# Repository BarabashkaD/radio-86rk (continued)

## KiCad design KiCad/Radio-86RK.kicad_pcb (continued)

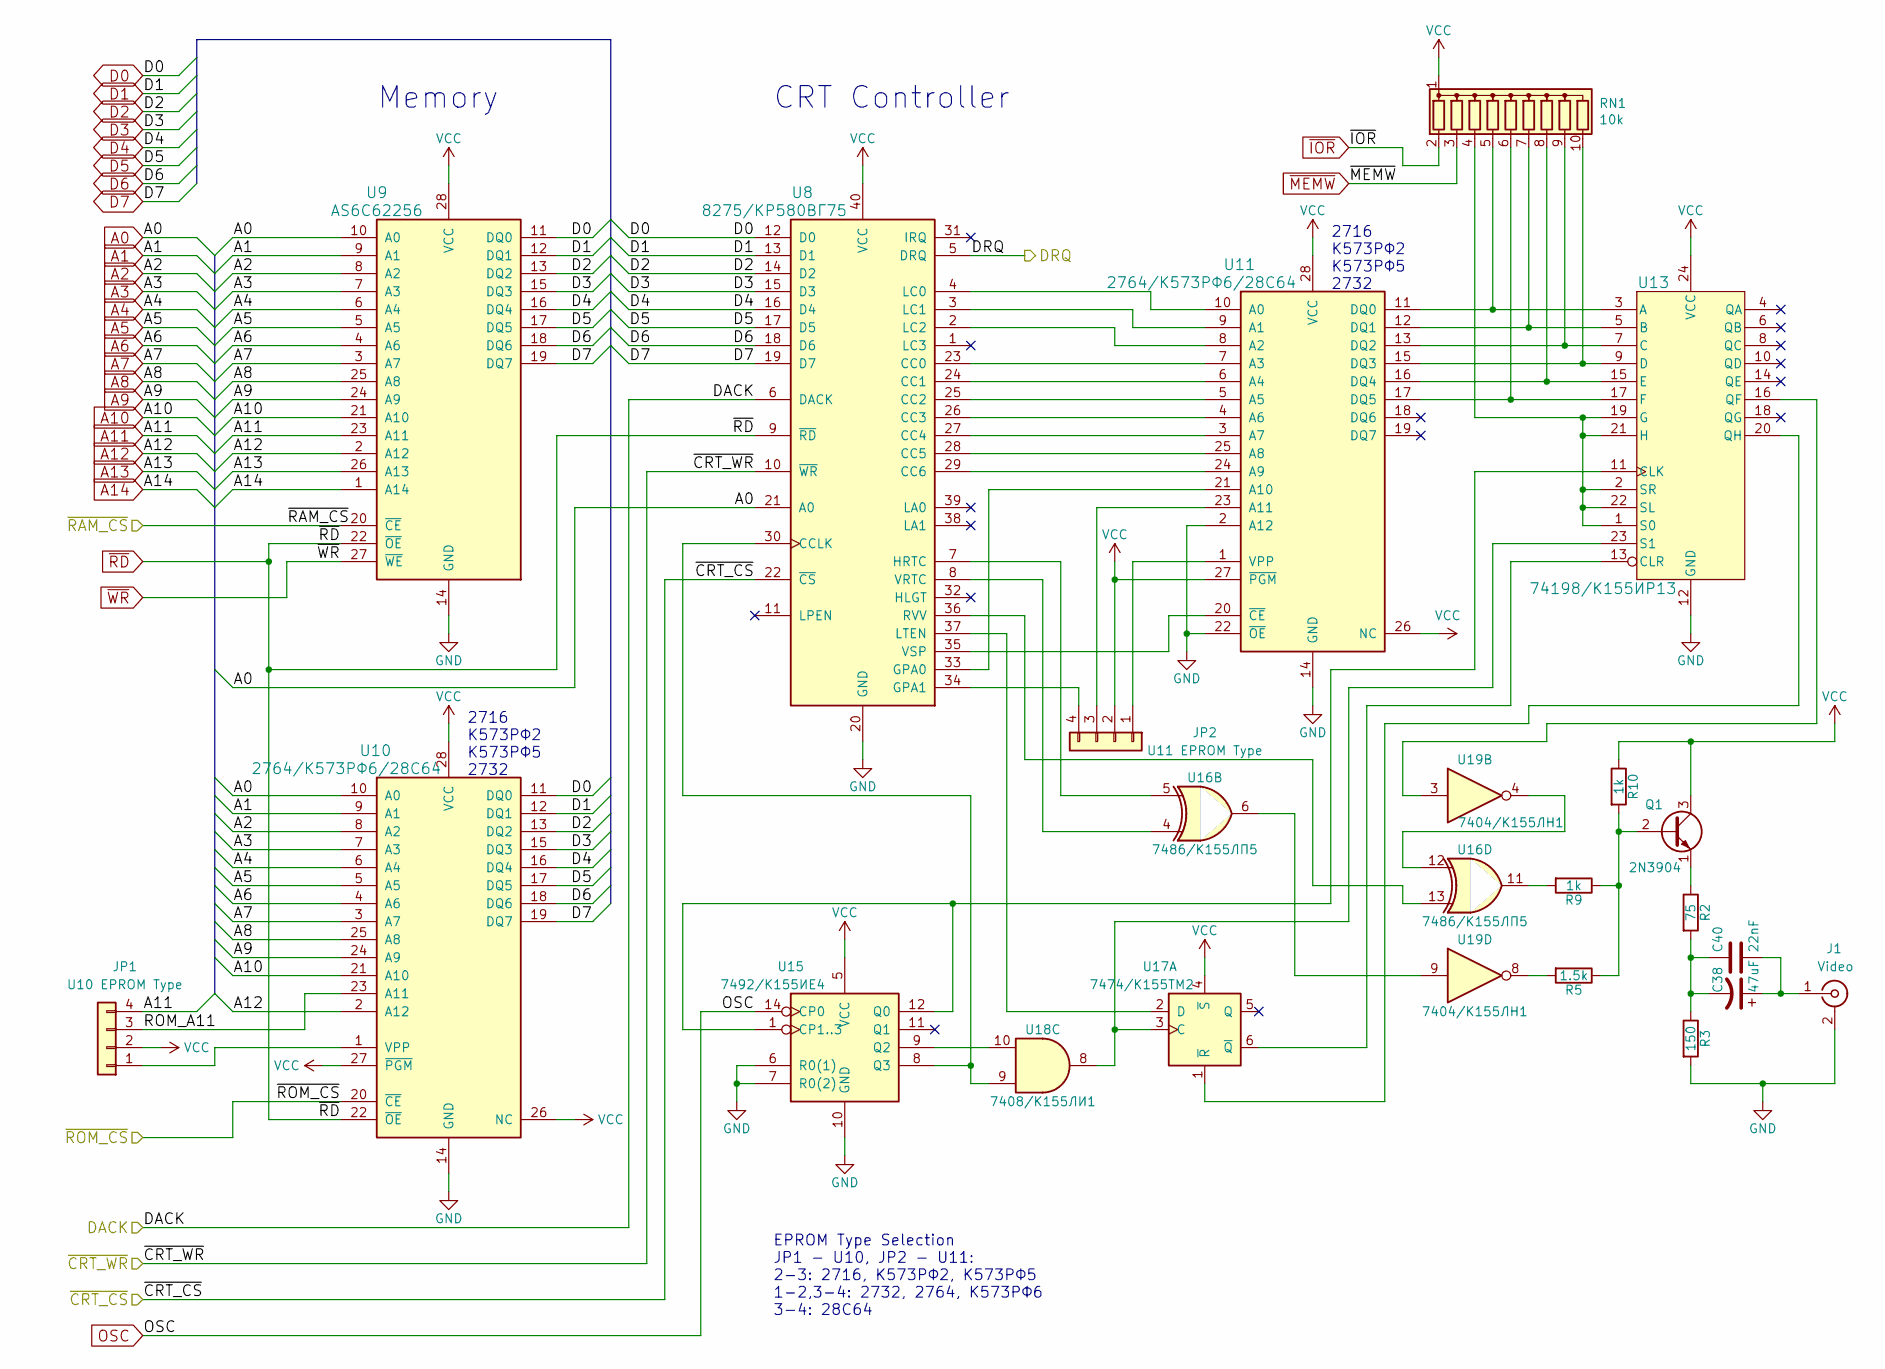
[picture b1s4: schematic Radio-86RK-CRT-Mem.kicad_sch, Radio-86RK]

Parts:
C38: 47uF; Cap_Elec_Radial_6.3mm
C40: 22nF; Cap_Cer_508
J1: Video; Conn_RCA_Right
JP1: U10 EPROM Type; Conn_Pin_Header_4x1_2.54mm
JP2: U11 EPROM Type; Conn_Pin_Header_4x1_2.54mm
Q1: 2N3904; Transistor_TO92_EBC_254
R2: 75; Res_762
R3: 150; Res_762
R5: 1.5k; Res_762
R9, R10: 1k; Res_762
RN1: 10k; Conn_SIL10
U8: 8275/КР580ВГ75; IC_DIP40_600
U9: AS6C62256; IC_DIP28_600
U10, U11: 2764/К573РФ6/28C64; IC_DIP28_600
U13: 74198/К155ИР13; IC_DIP24_600
U15: 7492/К155ИЕ4; IC_DIP14_300
U16: 7486/К155ЛП5; IC_DIP14_300
U17: 7474/К155ТМ2; IC_DIP14_300
U18: 7408/К155ЛИ1; IC_DIP14_300
U19: 7404/К155ЛН1; IC_DIP14_300

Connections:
/CRT_Memory/ROM_A11: JP1.3, U10.23 (A11)
/DACK: U8.6 (DACK); also elsewhere on the board
/DRQ: U8.5 (DRQ); also elsewhere on the board
/~CRT_CS: U8.22 (~CS); also elsewhere on the board
/~CRT_WR: U8.10 (~WR); also elsewhere on the board
/~RAM_CS: U9.20 (~CE); also elsewhere on the board
/~ROM_CS: U10.20 (~CE); also elsewhere on the board
A0: U8.21 (A0), U9.10 (A0), U10.10 (A0); also elsewhere on the board
A1: U9.9 (A1), U10.9 (A1); also elsewhere on the board
A2: U9.8 (A2), U10.8 (A2); also elsewhere on the board
A3: U9.7 (A3), U10.7 (A3); also elsewhere on the board
A4: U9.6 (A4), U10.6 (A4); also elsewhere on the board
A5: U9.5 (A5), U10.5 (A5); also elsewhere on the board
A6: U9.4 (A6), U10.4 (A6); also elsewhere on the board
A7: U9.3 (A7), U10.3 (A7); also elsewhere on the board
A8: U9.25 (A8), U10.25 (A8); also elsewhere on the board
A9: U9.24 (A9), U10.24 (A9); also elsewhere on the board
A10: U9.21 (A10), U10.21 (A10); also elsewhere on the board
A11: JP1.4, U9.23 (A11); also elsewhere on the board
A12: U9.2 (A12), U10.2 (A12); also elsewhere on the board
A13: U9.26 (A13); also elsewhere on the board
A14: U9.1 (A14); also elsewhere on the board
D0: U8.12 (D0), U9.11 (DQ0), U10.11 (DQ0); also elsewhere on the board
D1: U8.13 (D1), U9.12 (DQ1), U10.12 (DQ1); also elsewhere on the board
D2: U8.14 (D2), U9.13 (DQ2), U10.13 (DQ2); also elsewhere on the board
D3: U8.15 (D3), U9.15 (DQ3), U10.15 (DQ3); also elsewhere on the board
D4: U8.16 (D4), U9.16 (DQ4), U10.16 (DQ4); also elsewhere on the board
D5: U8.17 (D5), U9.17 (DQ5), U10.17 (DQ5); also elsewhere on the board
D6: U8.18 (D6), U9.18 (DQ6), U10.18 (DQ6); also elsewhere on the board
D7: U8.19 (D7), U9.19 (DQ7), U10.19 (DQ7); also elsewhere on the board
GND: J1.2 (Ext), R3.2, U8.20 (GND), U9.14 (GND), U10.14 (GND), U11.2 (A12), U11.14 (GND), U11.22 (~OE), U13.12 (GND), U15.6 (R0(1)), U15.7 (R0(2)), U15.10 (GND); also elsewhere on the board
unnamed: C38.1, C40.2, J1.1 (In)
unnamed: C38.2, C40.1, R2.2, R3.1
unnamed: JP1.1, U10.1 (VPP)
unnamed: JP2.3, U11.23 (A11)
unnamed: Q1.1 (E), R2.1
unnamed: Q1.2 (B), R5.1, R9.1, R10.2
unnamed: R5.2, U19.8
unnamed: R9.2, U16.11
unnamed: RN1.4 (R3), U13.1 (S0), U13.2 (SR), U13.19 (G), U13.21 (H), U13.22 (SL)
unnamed: RN1.5 (R4), U11.11 (DQ0), U13.3 (A)
unnamed: RN1.6 (R5), U11.17 (DQ5), U13.17 (F)
unnamed: RN1.7 (R6), U11.12 (DQ1), U13.5 (B)
unnamed: RN1.8 (R7), U11.16 (DQ4), U13.15 (E)
unnamed: RN1.9 (R8), U11.13 (DQ2), U13.7 (C)
unnamed: RN1.10 (R9), U11.15 (DQ3), U13.9 (D)
unnamed: U8.2 (LC2), U11.8 (A2)
unnamed: U8.3 (LC1), U11.9 (A1)
unnamed: U8.4 (LC0), U11.10 (A0)
unnamed: U8.23 (CC0), U11.7 (A3)
unnamed: U8.24 (CC1), U11.6 (A4)
unnamed: U8.25 (CC2), U11.5 (A5)
unnamed: U8.26 (CC3), U11.4 (A6)
unnamed: U8.27 (CC4), U11.3 (A7)
unnamed: U8.28 (CC5), U11.25 (A8)
unnamed: U8.29 (CC6), U11.24 (A9)
unnamed: U8.33 (GPA0), U11.21 (A10)
unnamed: JP2.4, U8.34 (GPA1)
unnamed: U8.35 (VSP), U11.20 (~CE)
unnamed: JP2.1, U11.1 (VPP)
unnamed: U13.11 (CLK), U15.1 (CP1..3), U15.12 (Q0)
unnamed: U13.13 (CLR), U17.6 (~Q)
unnamed: U13.16 (QF), U19.3
unnamed: U13.20 (QH), U17.1 (~R)
unnamed: U13.23 (S1), U17.3 (C), U18.8
unnamed: U8.30 (CCLK), U15.8 (Q3), U18.9
unnamed: U15.9 (Q2), U18.10
unnamed: U8.8 (VRTC), U16.4
unnamed: U8.7 (HRTC), U16.5
unnamed: U16.6, U19.9
unnamed: U16.12, U19.4
unnamed: U8.36 (RVV), U16.13
unnamed: U8.37 (LTEN), U17.2 (D)
OSC: U15.14 (CP0); also elsewhere on the board
VCC: JP1.2, JP2.2, Q1.3 (C), R10.1, RN1.1 (common), U8.40 (VCC), U9.28 (VCC), U10.26 (NC), U10.27 (~PGM), U10.28 (VCC), U11.26 (NC), U11.27 (~PGM), U11.28 (VCC), U13.24 (VCC), U15.5 (VCC), U17.4 (~S); also elsewhere on the board
~IOR: RN1.2 (R1); also elsewhere on the board
~MEMW: RN1.3 (R2); also elsewhere on the board
~RD: U8.9 (~RD), U9.22 (~OE), U10.22 (~OE); also elsewhere on the board
~WR: U9.27 (~WE); also elsewhere on the board

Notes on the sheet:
EPROM Type Selection JP1 - U10, JP2 - U11: 2-3: 2716, К573РФ2, К573РФ5 1-2,3-4: 2732, 2764, К573РФ6 3-4: 28C64
2716 К573РФ2 К573РФ5 2732
Memory
CRT Controller

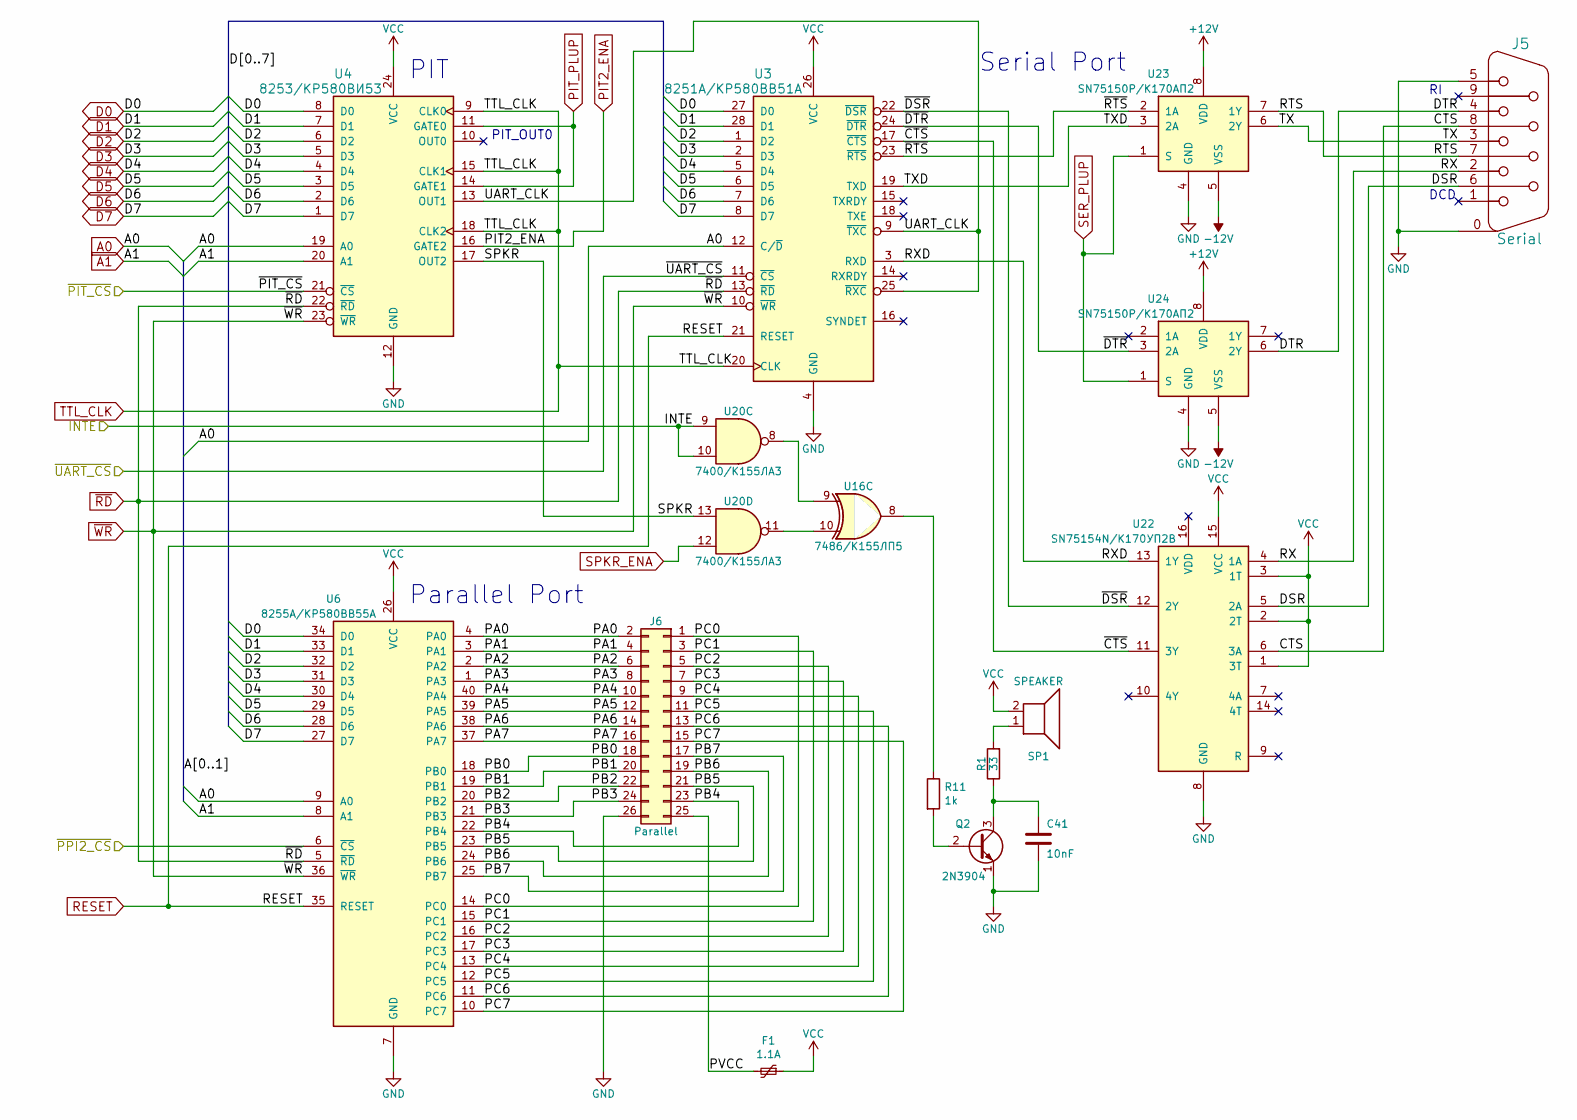
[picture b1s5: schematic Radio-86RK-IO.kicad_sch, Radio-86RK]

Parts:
C41: 10nF; Cap_Cer_508
F1: 1.1A; Cap_Cer_508
J5: Serial; Conn_Dsub_DE9M
J6: Parallel; Conn_Pin_Header_13x2_2.54mm_Shrouded
Q2: 2N3904; Transistor_TO92_EBC_254
R1: 33; Res_762
R11: 1k; Res_762
SP1: SPEAKER; Speaker_12mm
U3: 8251A/КР580ВВ51А; IC_DIP28_600
U4: 8253/КР580ВИ53; IC_DIP24_600
U6: 8255A/КР580ВВ55А; IC_DIP40_600
U16: 7486/К155ЛП5; IC_DIP14_300
U20: 7400/К155ЛА3; IC_DIP14_300
U22: SN75154N/К170УП2В; IC_DIP16_300
U23, U24: SN75150P/К170АП2; IC_DIP8_300

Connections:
+12V: U23.8 (VDD), U24.8 (VDD); also elsewhere on the board
-12V: U23.5 (VSS), U24.5 (VSS); also elsewhere on the board
/INTE: U20.9, U20.10; also elsewhere on the board
/Input_Output/CTS: J5.8, U22.6 (3A)
/Input_Output/DSR: J5.6, U22.5 (2A)
/Input_Output/DTR: J5.4, U24.6 (2Y)
/Input_Output/PA0: J6.2, U6.4 (PA0)
/Input_Output/PA1: J6.4, U6.3 (PA1)
/Input_Output/PA2: J6.6, U6.2 (PA2)
/Input_Output/PA3: J6.8, U6.1 (PA3)
/Input_Output/PA4: J6.10, U6.40 (PA4)
/Input_Output/PA5: J6.12, U6.39 (PA5)
/Input_Output/PA6: J6.14, U6.38 (PA6)
/Input_Output/PA7: J6.16, U6.37 (PA7)
/Input_Output/PB0: J6.18, U6.18 (PB0)
/Input_Output/PB1: J6.20, U6.19 (PB1)
/Input_Output/PB2: J6.22, U6.20 (PB2)
/Input_Output/PB3: J6.24, U6.21 (PB3)
/Input_Output/PB4: J6.23, U6.22 (PB4)
/Input_Output/PB5: J6.21, U6.23 (PB5)
/Input_Output/PB6: J6.19, U6.24 (PB6)
/Input_Output/PB7: J6.17, U6.25 (PB7)
/Input_Output/PC0: J6.1, U6.14 (PC0)
/Input_Output/PC1: J6.3, U6.15 (PC1)
/Input_Output/PC2: J6.5, U6.16 (PC2)
/Input_Output/PC3: J6.7, U6.17 (PC3)
/Input_Output/PC4: J6.9, U6.13 (PC4)
/Input_Output/PC5: J6.11, U6.12 (PC5)
/Input_Output/PC6: J6.13, U6.11 (PC6)
/Input_Output/PC7: J6.15, U6.10 (PC7)
/Input_Output/PVCC: F1.2, J6.25
/Input_Output/RTS: J5.7, U23.7 (1Y)
/Input_Output/RX: J5.2, U22.4 (1A)
/Input_Output/RXD: U3.3 (RXD), U22.13 (1Y)
/Input_Output/SPKR: U4.17 (OUT2), U20.13
/Input_Output/TX: J5.3, U23.6 (2Y)
/Input_Output/TXD: U3.19 (TXD), U23.3 (2A)
/Input_Output/UART_CLK: U3.9 (~TXC), U3.25 (~RXC), U4.13 (OUT1)
/Input_Output/~CTS: U3.17 (~CTS), U22.11 (3Y)
/Input_Output/~DSR: U3.22 (~DSR), U22.12 (2Y)
/Input_Output/~DTR: U3.24 (~DTR), U24.3 (2A)
/Input_Output/~RTS: U3.23 (~RTS), U23.2 (1A)
/~PIT_CS: U4.21 (~CS); also elsewhere on the board
/~PPI2_CS: U6.6 (~CS); also elsewhere on the board
/~UART_CS: U3.11 (~CS); also elsewhere on the board
A0: U3.12 (C/~D), U4.19 (A0), U6.9 (A0); also elsewhere on the board
A1: U4.20 (A1), U6.8 (A1); also elsewhere on the board
D0: U3.27 (D0), U4.8 (D0), U6.34 (D0); also elsewhere on the board
D1: U3.28 (D1), U4.7 (D1), U6.33 (D1); also elsewhere on the board
D2: U3.1 (D2), U4.6 (D2), U6.32 (D2); also elsewhere on the board
D3: U3.2 (D3), U4.5 (D3), U6.31 (D3); also elsewhere on the board
D4: U3.5 (D4), U4.4 (D4), U6.30 (D4); also elsewhere on the board
D5: U3.6 (D5), U4.3 (D5), U6.29 (D5); also elsewhere on the board
D6: U3.7 (D6), U4.2 (D6), U6.28 (D6); also elsewhere on the board
D7: U3.8 (D7), U4.1 (D7), U6.27 (D7); also elsewhere on the board
GND: C41.2, J5.0 (GND), J5.5, J6.26, Q2.1 (E), U3.4 (GND), U4.12 (GND), U6.7 (GND), U22.8 (GND), U23.4 (GND), U24.4 (GND); also elsewhere on the board
unnamed: C41.1, Q2.3 (C), R1.1
unnamed: Q2.2 (B), R11.2
unnamed: R1.2, SP1.1
unnamed: R11.1, U16.8
unnamed: U16.9, U20.8
unnamed: U16.10, U20.11
PIT2_ENA: U4.16 (GATE2); also elsewhere on the board
PIT_PLUP: U4.11 (GATE0), U4.14 (GATE1); also elsewhere on the board
RESET: U3.21 (RESET), U6.35 (RESET); also elsewhere on the board
SER_PLUP: U23.1 (S), U24.1 (S); also elsewhere on the board
SPKR_ENA: U20.12; also elsewhere on the board
TTL_CLK: U3.20 (CLK), U4.9 (CLK0), U4.15 (CLK1), U4.18 (CLK2); also elsewhere on the board
VCC: F1.1, SP1.2, U3.26 (VCC), U4.24 (VCC), U6.26 (VCC), U22.1 (3T), U22.2 (2T), U22.3 (1T), U22.15 (VCC); also elsewhere on the board
~RD: U3.13 (~RD), U4.22 (~RD), U6.5 (~RD); also elsewhere on the board
~WR: U3.10 (~WR), U4.23 (~WR), U6.36 (~WR); also elsewhere on the board

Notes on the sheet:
PIT
DCD
PIT_OUT0
Parallel Port
Serial Port

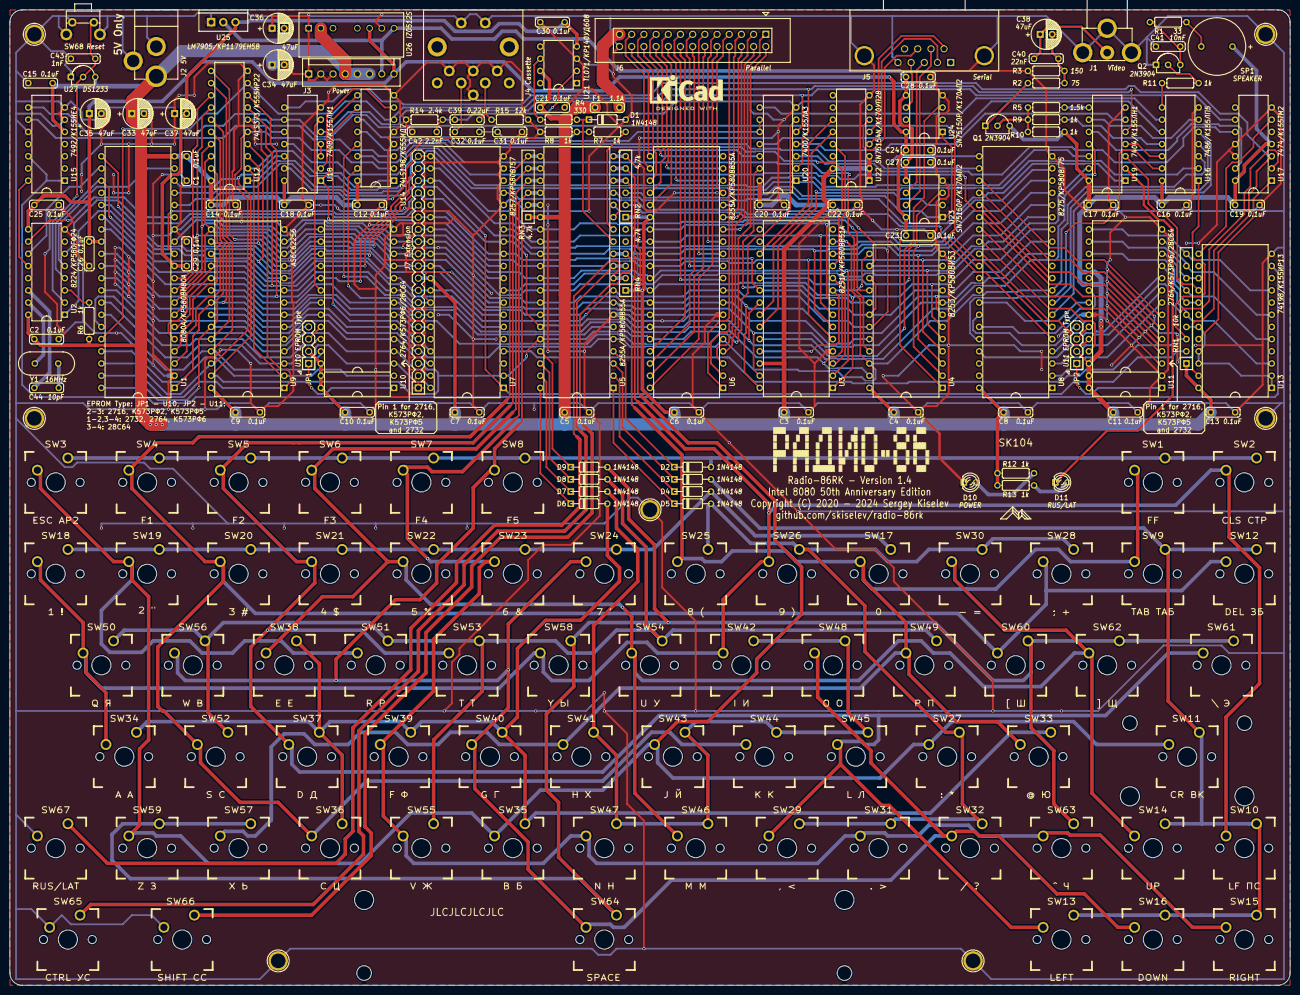
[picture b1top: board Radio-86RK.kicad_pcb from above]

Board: 2 copper layers, 266.7 x 203.2 mm, 191 parts (0 on the bottom side), 200 nets.
